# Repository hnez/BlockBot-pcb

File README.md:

BlockBot - Housing 3D-Designs
=============================

This repository contains all PCB design files.

All designs are created with the KiCad EDA suite.

The directory structure is as follow:

- blocks - Brick PCB
- dk_base - Millable PCB for the "denmark base" robot
- panel - Panelized layout that combines bricks and remote into a single file for cheaper ordering
- remote - Collector unit PCB

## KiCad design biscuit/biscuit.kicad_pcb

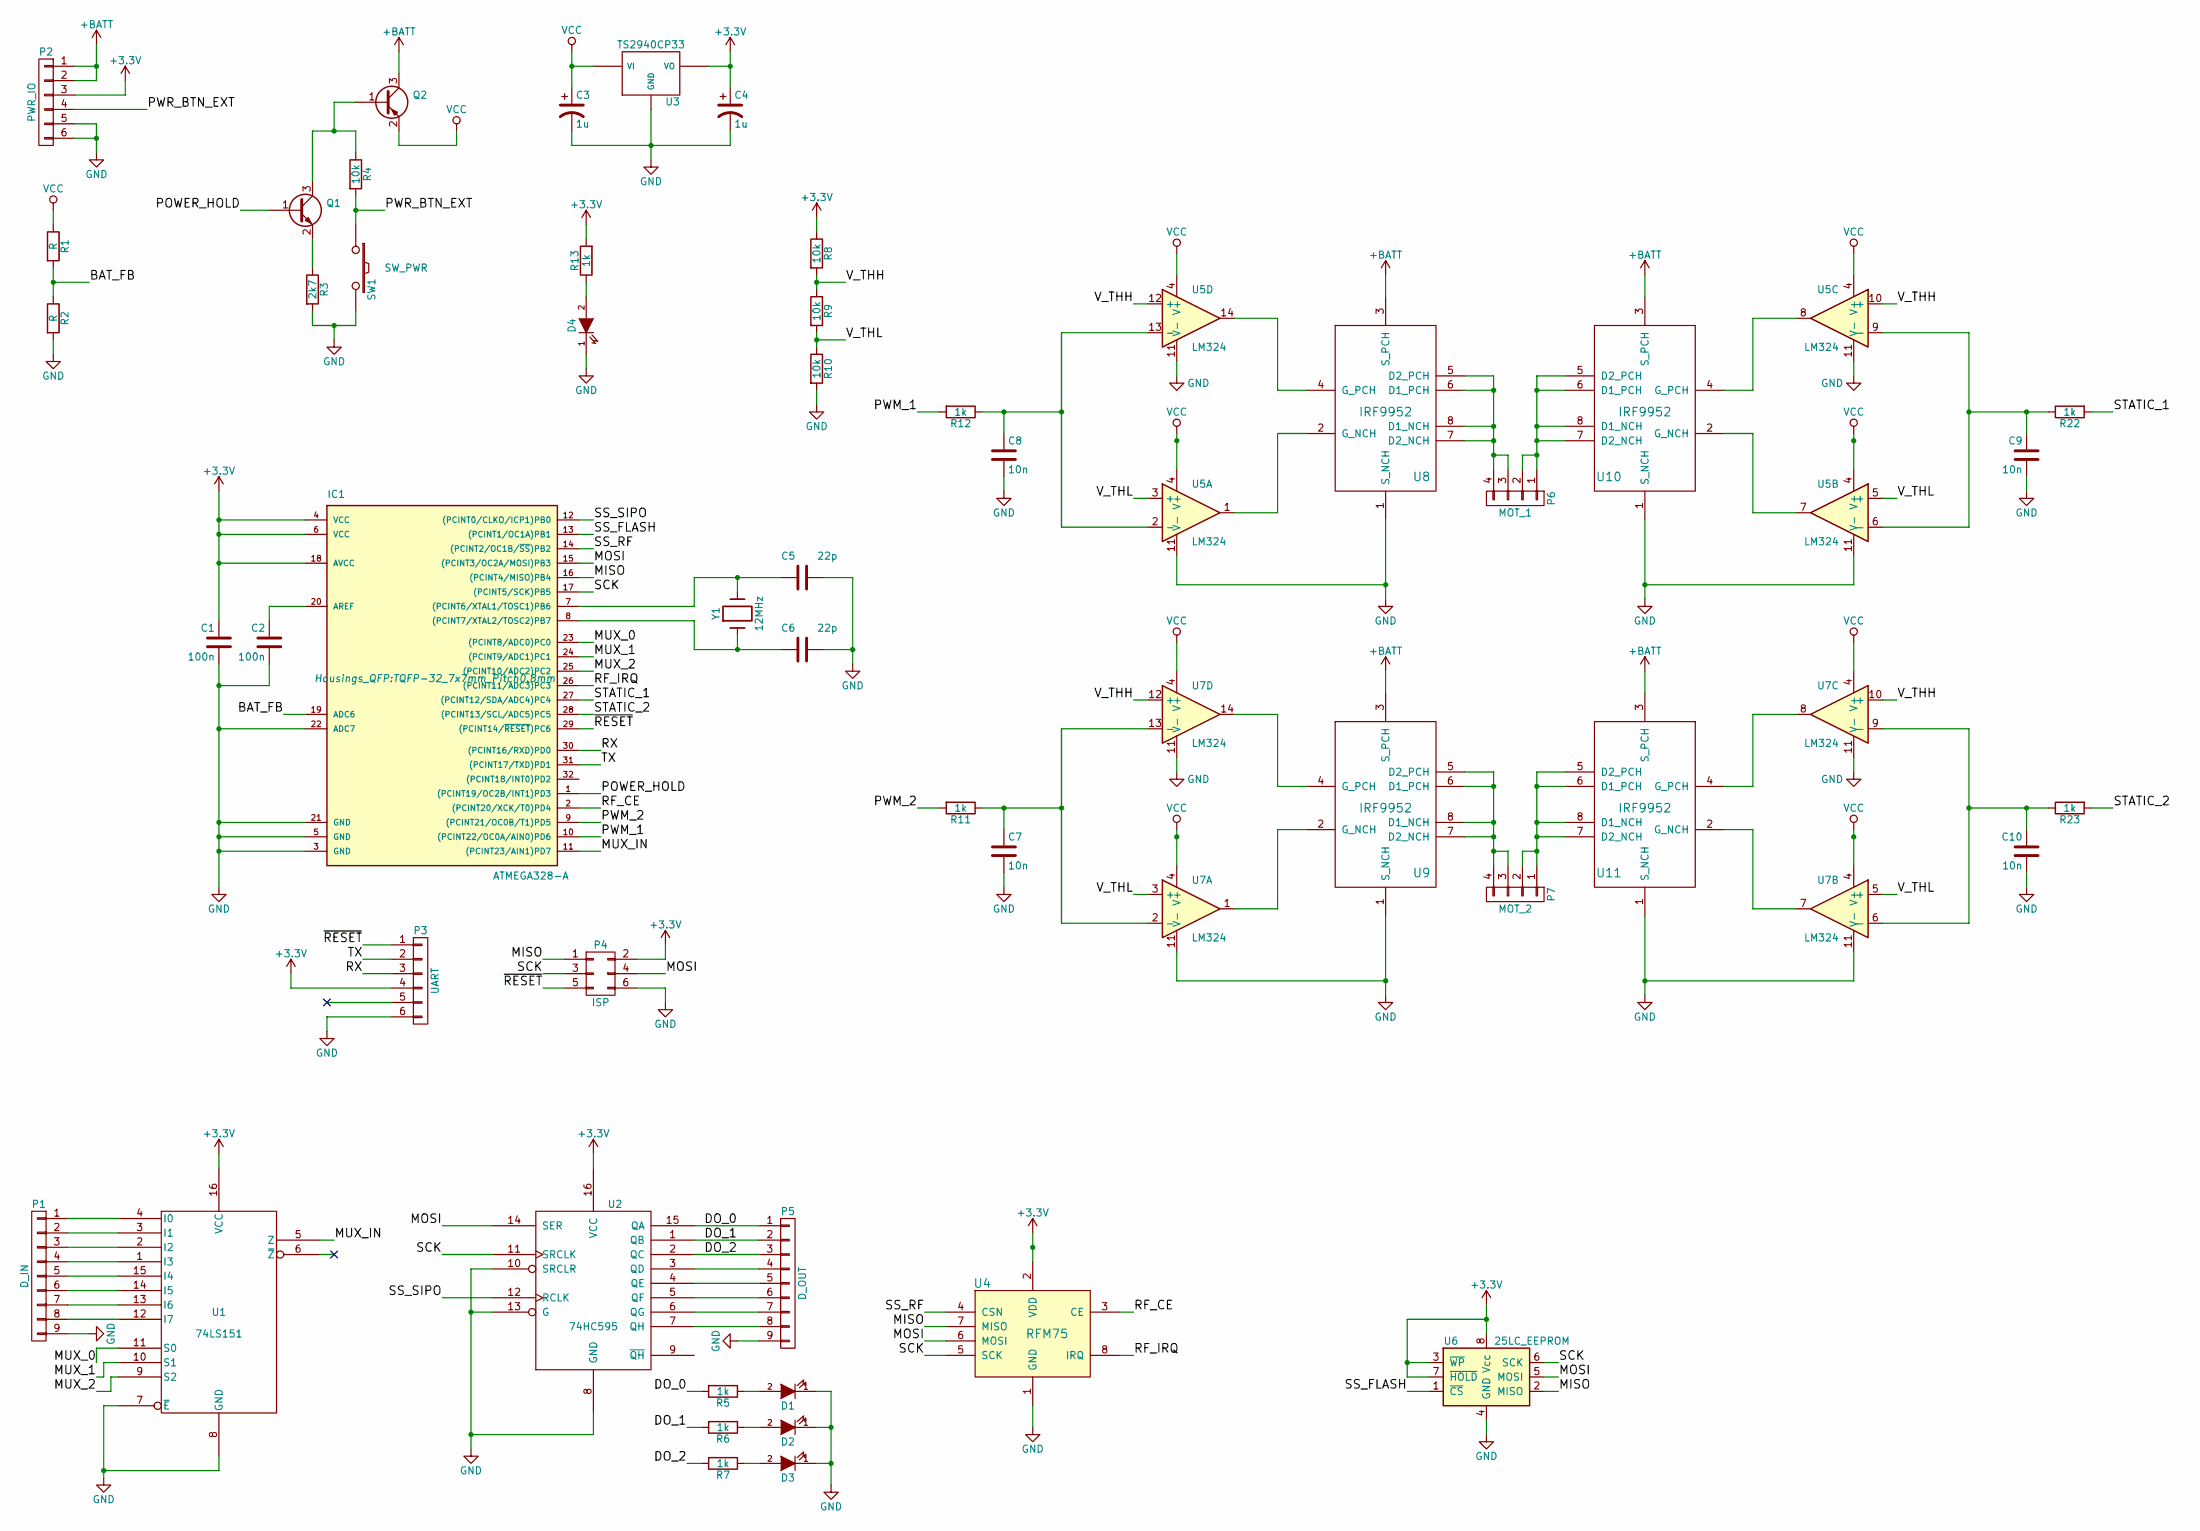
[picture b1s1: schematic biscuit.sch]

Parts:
C1, C2: 100n; C_0805
C3, C4: 1u; TantalC_SizeA_EIA-3216_Reflow
C5, C6: 22p; C_0805
C7, C8, C9, C10: 10n; C_0805
D1, D2, D3, D4: LED; LED_0805
IC1: ATMEGA328-A; TQFP-32_7x7mm_Pitch0.8mm
P1: D_IN; Pin_Header_Straight_1x09
P2: PWR_IO; Pin_Header_Straight_1x06
P3: UART; Pin_Header_Straight_1x06
P4: ISP; Pin_Header_Straight_2x03
P5: D_OUT; Pin_Header_Straight_1x09
P6: MOT_1; Pin_Header_Straight_1x04
P7: MOT_2; Pin_Header_Straight_1x04
Q1: Q_NPN_BEC; SOT-23
Q2: Q_PNP_BEC; SOT-23
R1, R2: R; R_0805
R3: 2k7; R_0805
R4, R8, R9, R10: 10k; R_0805
R5, R6, R7, R11, R12, R13, R22, R23: 1k; R_0805
SW1: SW_PWR; Schurter_LSG_1301
U1: 74LS151; SO-16-N
U2: 74HC595; SO-16-N
U3: TS2940CP33; TO-252-2Lead
U4: RFM75
U5, U7: LM324; SOIC-14_N
U6: 25LC_EEPROM; SOIC-8-N
U8, U9, U10, U11: IRF9952; SOIC-8-N
Y1: 12MHz; Crystal_HC49-SD_SMD

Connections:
+3V3: C1.1, C4.1, IC1.4 (VCC), IC1.6 (VCC), IC1.18 (AVCC), P2.3, P3.4, P4.2, R8.1, R13.2, U1.16 (VCC), U2.16 (VCC), U3.3 (VO), U4.2 (VDD), U6.3 (~WP), U6.7 (~HOLD), U6.8 (Vcc)
+BATT: P2.1, P2.2, Q2.3 (C), U8.3 (S_PCH), U9.3 (S_PCH), U10.3 (S_PCH), U11.3 (S_PCH)
/BAT_FB: IC1.19 (ADC6), R1.2, R2.1
/DO_0: P5.1, R5.2, U2.15 (QA)
/DO_1: P5.2, R6.2, U2.1 (QB)
/DO_2: P5.3, R7.2, U2.2 (QC)
/MISO: IC1.16 ((PCINT4/MISO)PB4), P4.1, U4.7 (MISO), U6.2 (MISO)
/MOSI: IC1.15 ((PCINT3/OC2A/MOSI)PB3), P4.4, U2.14 (SER), U4.6 (MOSI), U6.5 (MOSI)
/MUX_0: IC1.23 ((PCINT8/ADC0)PC0), U1.11 (S0)
/MUX_1: IC1.24 ((PCINT9/ADC1)PC1), U1.10 (S1)
/MUX_2: IC1.25 ((PCINT10/ADC2)PC2), U1.9 (S2)
/MUX_IN: IC1.11 ((PCINT23/AIN1)PD7), U1.5 (Z)
/POWER_HOLD: IC1.1 ((PCINT19/OC2B/INT1)PD3), Q1.1 (B)
/PWM_1: IC1.10 ((PCINT22/OC0A/AIN0)PD6), R12.2
/PWM_2: IC1.9 ((PCINT21/OC0B/T1)PD5), R11.2
/PWR_BTN_EXT: P2.4, R4.2, SW1.1
/RF_CE: IC1.2 ((PCINT20/XCK/T0)PD4), U4.3 (CE)
/RF_IRQ: IC1.26 ((PCINT11/ADC3)PC3), U4.8 (IRQ)
/RX: IC1.30 ((PCINT16/RXD)PD0), P3.3
/SCK: IC1.17 ((PCINT5/SCK)PB5), P4.3, U2.11 (SRCLK), U4.5 (SCK), U6.6 (SCK)
/SS_FLASH: IC1.13 ((PCINT1/OC1A)PB1), U6.1 (~CS)
/SS_RF: IC1.14 ((PCINT2/OC1B/~SS~)PB2), U4.4 (CSN)
/SS_SIPO: IC1.12 ((PCINT0/CLKO/ICP1)PB0), U2.12 (RCLK)
/STATIC_1: IC1.27 ((PCINT12/SDA/ADC4)PC4), R22.2
/STATIC_2: IC1.28 ((PCINT13/SCL/ADC5)PC5), R23.2
/TX: IC1.31 ((PCINT17/TXD)PD1), P3.2
/V_THH: R8.2, R9.1, U5.10 (+), U5.12 (+), U7.10 (+), U7.12 (+)
/V_THL: R9.2, R10.1, U5.3 (+), U5.5 (+), U7.3 (+), U7.5 (+)
/~RESET: IC1.29 ((PCINT14/~RESET~)PC6), P3.1, P4.5
GND: C1.2, C2.2, C3.2, C4.2, C5.1, C6.1, C7.2, C8.2, C9.2, C10.2, D1.1 (K), D2.1 (K), D3.1 (K), D4.1 (K), IC1.3 (GND), IC1.5 (GND), IC1.21 (GND), IC1.22 (ADC7), P1.9, P2.5, P2.6, P3.6, P4.6, P5.9, R2.2, R3.2, R10.2, SW1.2, U1.7 (~E), U1.8 (GND), U2.8 (GND), U2.10 (SRCLR), U2.13 (G), U3.2 (GND), U4.1 (GND), U5.11 (V-), U6.4 (GND), U7.11 (V-), U8.1 (S_NCH), U9.1 (S_NCH), U10.1 (S_NCH), U11.1 (S_NCH)
unnamed: C2.1, IC1.20 (AREF)
unnamed: C5.2, IC1.7 ((PCINT6/XTAL1/TOSC1)PB6), Y1.2
unnamed: C6.2, IC1.8 ((PCINT7/XTAL2/TOSC2)PB7), Y1.1
unnamed: C7.1, R11.1, U7.2 (-), U7.13 (-)
unnamed: C8.1, R12.1, U5.2 (-), U5.13 (-)
unnamed: C9.1, R22.1, U5.6 (-), U5.9 (-)
unnamed: C10.1, R23.1, U7.6 (-), U7.9 (-)
unnamed: D1.2 (A), R5.1
unnamed: D2.2 (A), R6.1
unnamed: D3.2 (A), R7.1
unnamed: D4.2 (A), R13.1
unnamed: P1.1, U1.4 (I0)
unnamed: P1.2, U1.3 (I1)
unnamed: P1.3, U1.2 (I2)
unnamed: P1.4, U1.1 (I3)
unnamed: P1.5, U1.15 (I4)
unnamed: P1.6, U1.14 (I5)
unnamed: P1.7, U1.13 (I6)
unnamed: P1.8, U1.12 (I7)
unnamed: P5.4, U2.3 (QD)
unnamed: P5.5, U2.4 (QE)
unnamed: P5.6, U2.5 (QF)
unnamed: P5.7, U2.6 (QG)
unnamed: P5.8, U2.7 (QH)
unnamed: P6.1, P6.2, U10.5 (D2_PCH), U10.6 (D1_PCH), U10.7 (D2_NCH), U10.8 (D1_NCH)
unnamed: P6.3, P6.4, U8.5 (D2_PCH), U8.6 (D1_PCH), U8.7 (D2_NCH), U8.8 (D1_NCH)
unnamed: P7.1, P7.2, U11.5 (D2_PCH), U11.6 (D1_PCH), U11.7 (D2_NCH), U11.8 (D1_NCH)
unnamed: P7.3, P7.4, U9.5 (D2_PCH), U9.6 (D1_PCH), U9.7 (D2_NCH), U9.8 (D1_NCH)
unnamed: Q1.2 (E), R3.1
unnamed: Q1.3 (C), Q2.1 (B), R4.1
unnamed: U5.1, U8.2 (G_NCH)
unnamed: U5.14, U8.4 (G_PCH)
unnamed: U7.1, U9.2 (G_NCH)
unnamed: U7.14, U9.4 (G_PCH)
unnamed: U5.7, U10.2 (G_NCH)
unnamed: U5.8, U10.4 (G_PCH)
unnamed: U7.7, U11.2 (G_NCH)
unnamed: U7.8, U11.4 (G_PCH)
VCC: C3.1, Q2.2 (E), R1.1, U3.1 (VI), U5.4 (V+), U7.4 (V+)

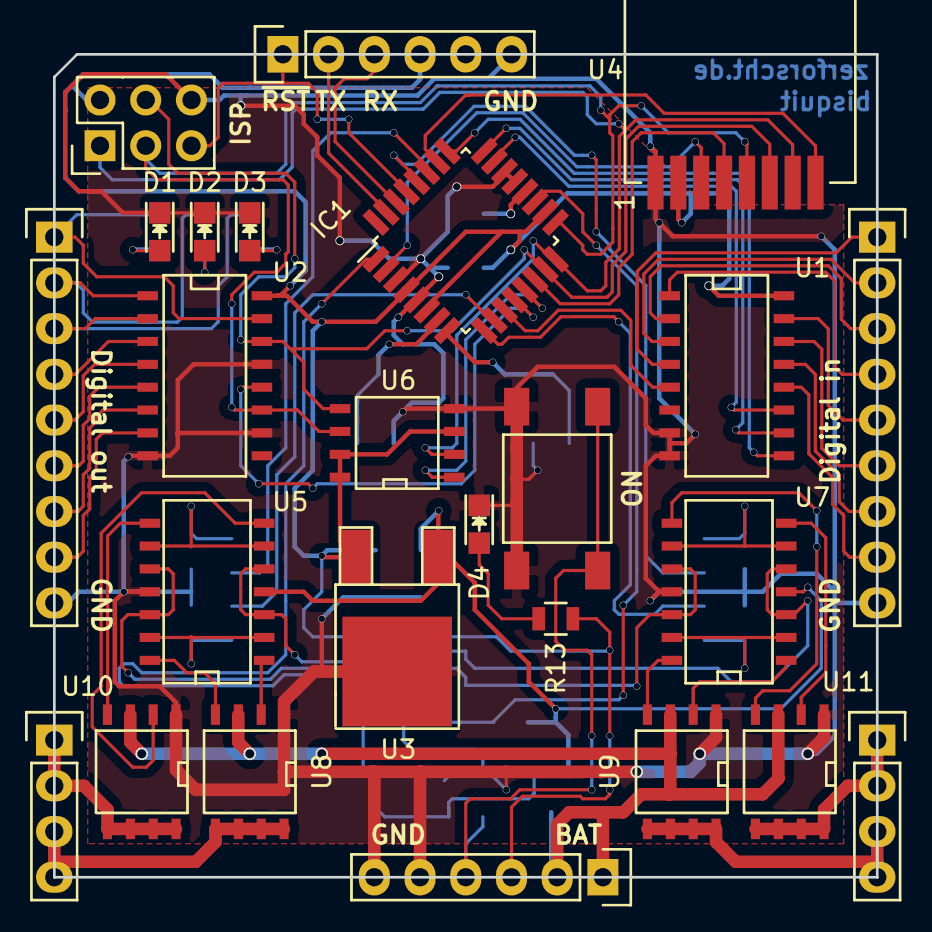
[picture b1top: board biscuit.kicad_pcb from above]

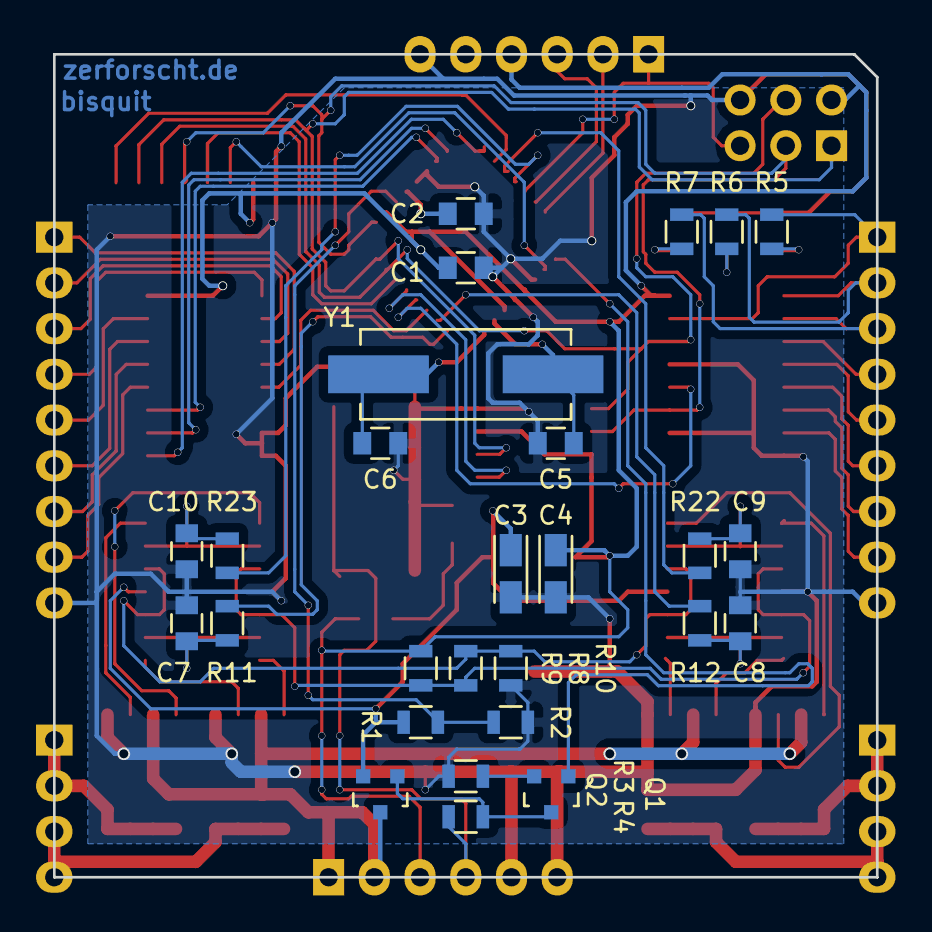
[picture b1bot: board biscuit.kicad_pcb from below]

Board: 2 copper layers, 45.7 x 45.7 mm, 52 parts (27 on the bottom side), 69 nets.

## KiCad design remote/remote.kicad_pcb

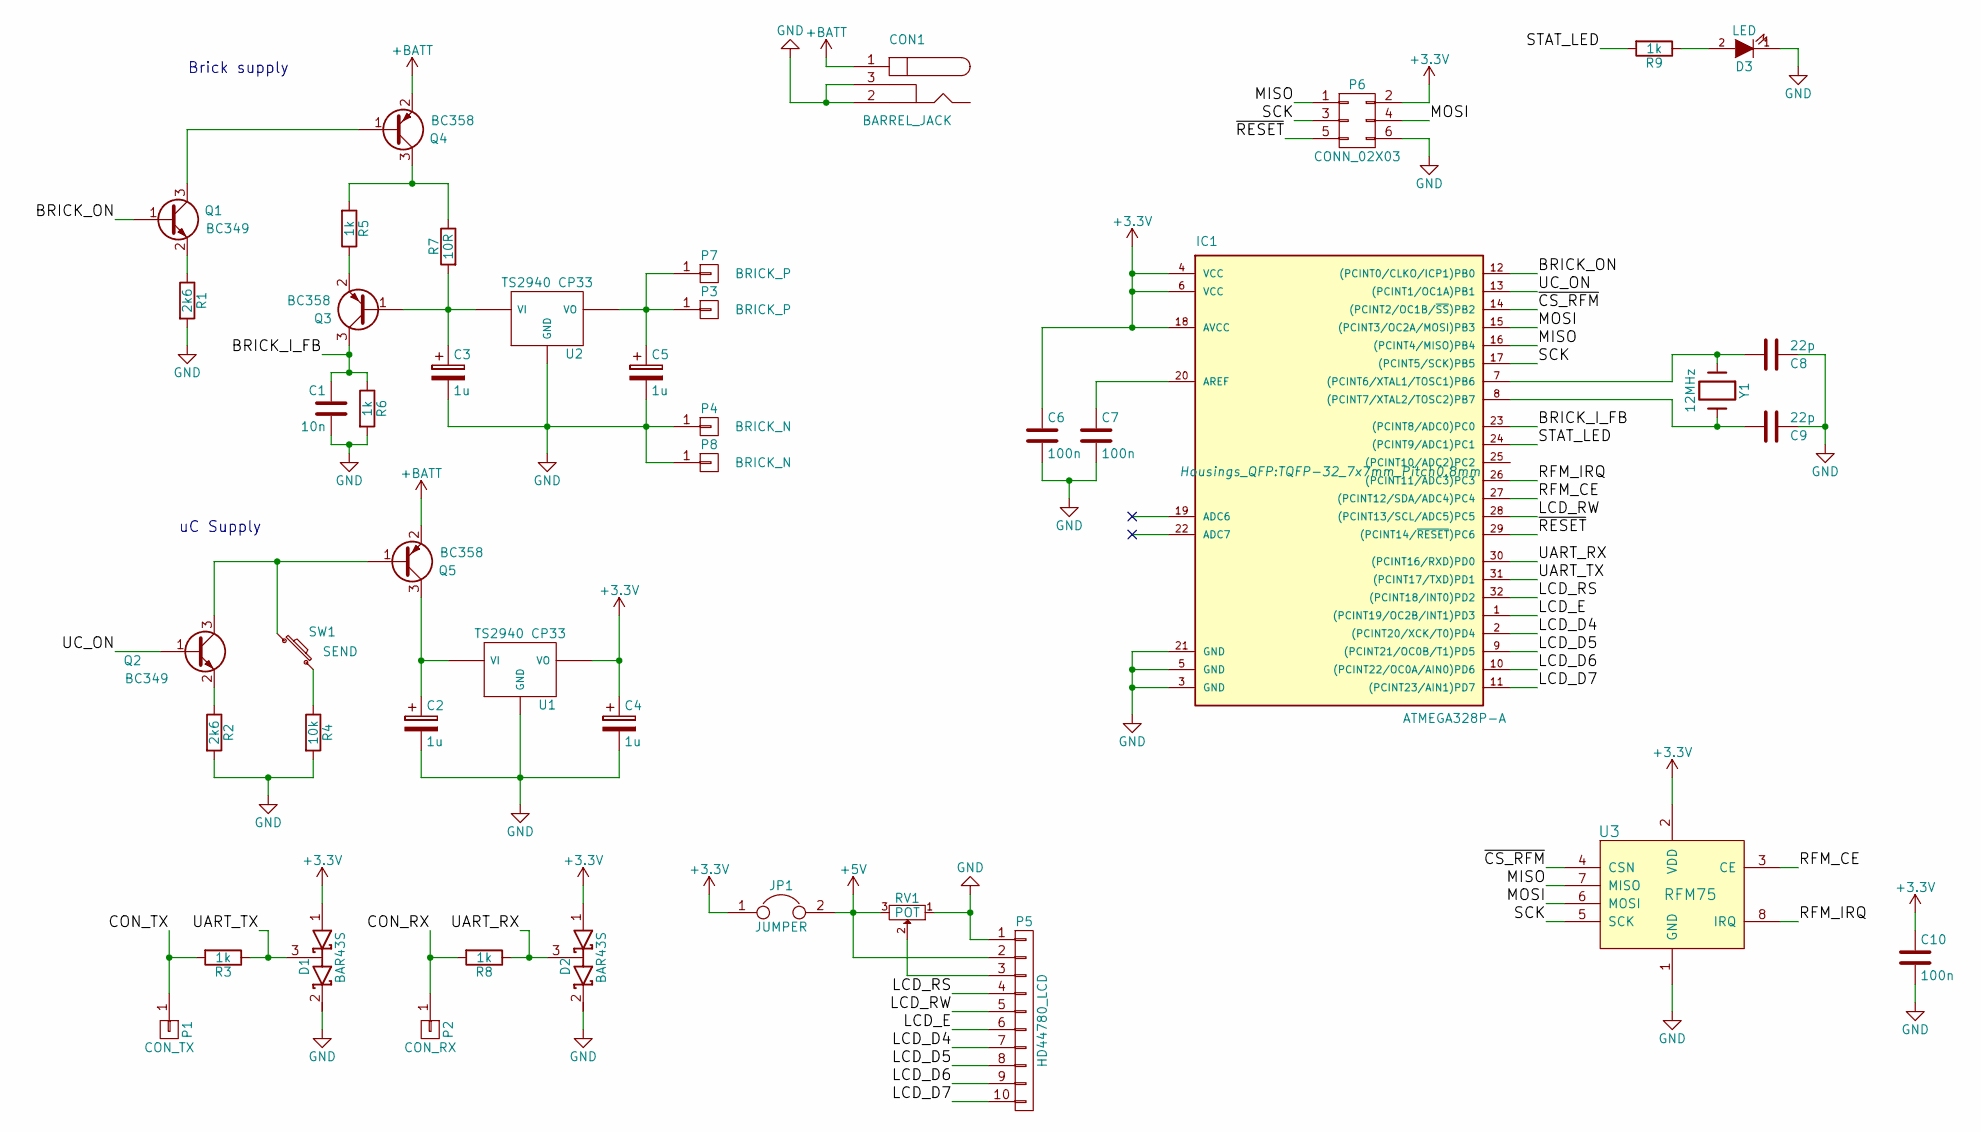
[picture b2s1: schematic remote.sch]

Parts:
C1: 10n; C_0805_HandSoldering
C2, C3, C4, C5: 1u; TantalC_SizeA_EIA-3216_HandSoldering
C6, C7, C10: 100n; C_0805_HandSoldering
C8, C9: 22p; C_0805_HandSoldering
CON1: BARREL_JACK
D1, D2: BAR43S; SOT-23
D3: LED; LED-3MM
IC1: ATMEGA328P-A; TQFP-32_7x7mm_Pitch0.8mm
JP1: JUMPER; R_0805_HandSoldering
P1: CON_TX; SmallFoilCon
P2: CON_RX; SmallFoilCon
P3, P7: BRICK_P; SmallFoilCon
P4, P8: BRICK_N; BigFoilCon
P5: HD44780_LCD; Pin_Header_Straight_1x10
P6: CONN_02X03; Pin_Header_Straight_2x03
Q1, Q2: BC349; SOT-23
Q3, Q4, Q5: BC358; SOT-23
R1, R2: 2k6; R_0805_HandSoldering
R3, R5, R6, R8, R9: 1k; R_0805_HandSoldering
R4: 10k; R_0805_HandSoldering
R7: 10R; R_0805_HandSoldering
RV1: POT; Cermet_Model23
SW1: SEND; Schurter_LSG_1301
U1, U2: TS2940 CP33; TO-252-2Lead
U3: RFM75
Y1: 12MHz; Crystal_HC49-U_Vertical

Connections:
+3V3: C4.1, C6.1, C10.1, D1.1 (A), D2.1 (A), IC1.4 (VCC), IC1.6 (VCC), IC1.18 (AVCC), JP1.1, P6.2, U1.VO, U3.2 (VDD)
+5V: JP1.2, P5.2, RV1.3
+BATT: CON1.1, Q4.2 (E), Q5.2 (E)
/BRICK_I_FB: C1.1, IC1.23 ((PCINT8/ADC0)PC0), Q3.3 (C), R6.1
/BRICK_ON: IC1.12 ((PCINT0/CLKO/ICP1)PB0), Q1.1 (B)
/CON_RX: P2.1, R8.2
/CON_TX: P1.1, R3.2
/LCD_D4: IC1.2 ((PCINT20/XCK/T0)PD4), P5.7
/LCD_D5: IC1.9 ((PCINT21/OC0B/T1)PD5), P5.8
/LCD_D6: IC1.10 ((PCINT22/OC0A/AIN0)PD6), P5.9
/LCD_D7: IC1.11 ((PCINT23/AIN1)PD7), P5.10
/LCD_E: IC1.1 ((PCINT19/OC2B/INT1)PD3), P5.6
/LCD_RS: IC1.32 ((PCINT18/INT0)PD2), P5.4
/LCD_RW: IC1.28 ((PCINT13/SCL/ADC5)PC5), P5.5
/MISO: IC1.16 ((PCINT4/MISO)PB4), P6.1, U3.7 (MISO)
/MOSI: IC1.15 ((PCINT3/OC2A/MOSI)PB3), P6.4, U3.6 (MOSI)
/RFM_CE: IC1.27 ((PCINT12/SDA/ADC4)PC4), U3.3 (CE)
/RFM_IRQ: IC1.26 ((PCINT11/ADC3)PC3), U3.8 (IRQ)
/SCK: IC1.17 ((PCINT5/SCK)PB5), P6.3, U3.5 (SCK)
/STAT_LED: IC1.24 ((PCINT9/ADC1)PC1), R9.2
/UART_RX: D2.3 (common), IC1.30 ((PCINT16/RXD)PD0), R8.1
/UART_TX: D1.3 (common), IC1.31 ((PCINT17/TXD)PD1), R3.1
/UC_ON: IC1.13 ((PCINT1/OC1A)PB1), Q2.1 (B)
/~CS_RFM: IC1.14 ((PCINT2/OC1B/~SS~)PB2), U3.4 (CSN)
/~RESET: IC1.29 ((PCINT14/~RESET~)PC6), P6.5
GND: C1.2, C2.2, C3.2, C4.2, C5.2, C6.2, C7.2, C8.1, C9.1, C10.2, CON1.2, CON1.3, D1.2 (K), D2.2 (K), D3.1 (K), IC1.3 (GND), IC1.5 (GND), IC1.21 (GND), P4.1, P5.1, P6.6, P8.1, R1.2, R2.2, R4.2, R6.2, RV1.1, U1.GND, U2.GND, U3.1 (GND)
unnamed: C2.1, Q5.3 (C), U1.VI
unnamed: C3.1, Q3.1 (B), R7.2, U2.VI
unnamed: C5.1, P3.1, P7.1, U2.VO
unnamed: C7.1, IC1.20 (AREF)
unnamed: C8.2, IC1.7 ((PCINT6/XTAL1/TOSC1)PB6), Y1.1
unnamed: C9.2, IC1.8 ((PCINT7/XTAL2/TOSC2)PB7), Y1.2
unnamed: D3.2 (A), R9.1
unnamed: P5.3, RV1.2
unnamed: Q1.2 (E), R1.1
unnamed: Q1.3 (C), Q4.1 (B)
unnamed: Q2.2 (E), R2.1
unnamed: Q2.3 (C), Q5.1 (B), SW1.1
unnamed: Q3.2 (E), R5.1
unnamed: Q4.3 (C), R5.2, R7.1
unnamed: R4.1, SW1.2

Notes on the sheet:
Brick supply
uC Supply

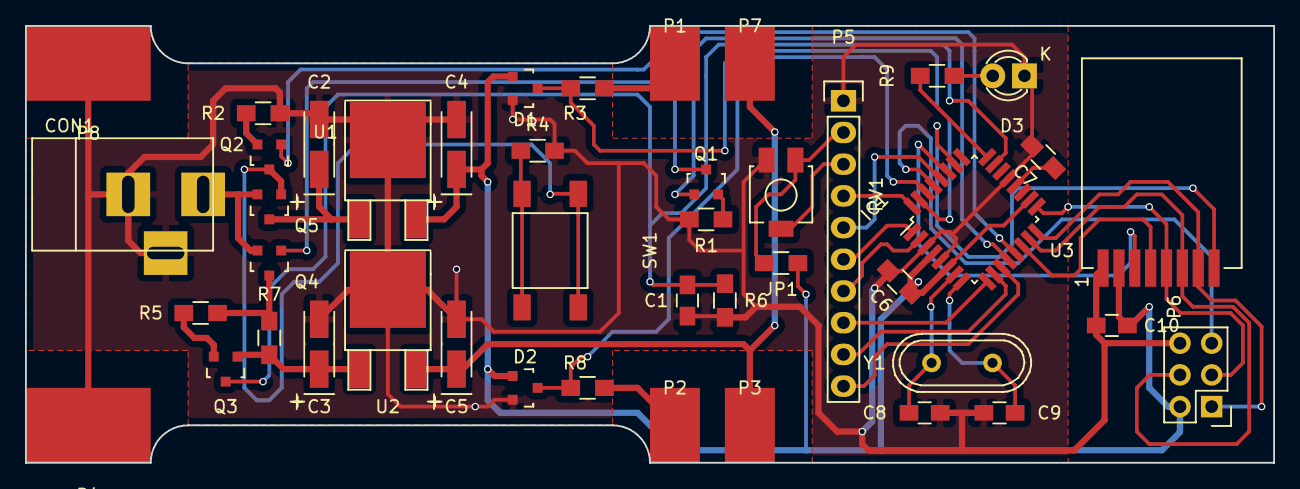
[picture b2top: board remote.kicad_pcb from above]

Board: 2 copper layers, 100.0 x 35.0 mm, 44 parts (0 on the bottom side), 41 nets.

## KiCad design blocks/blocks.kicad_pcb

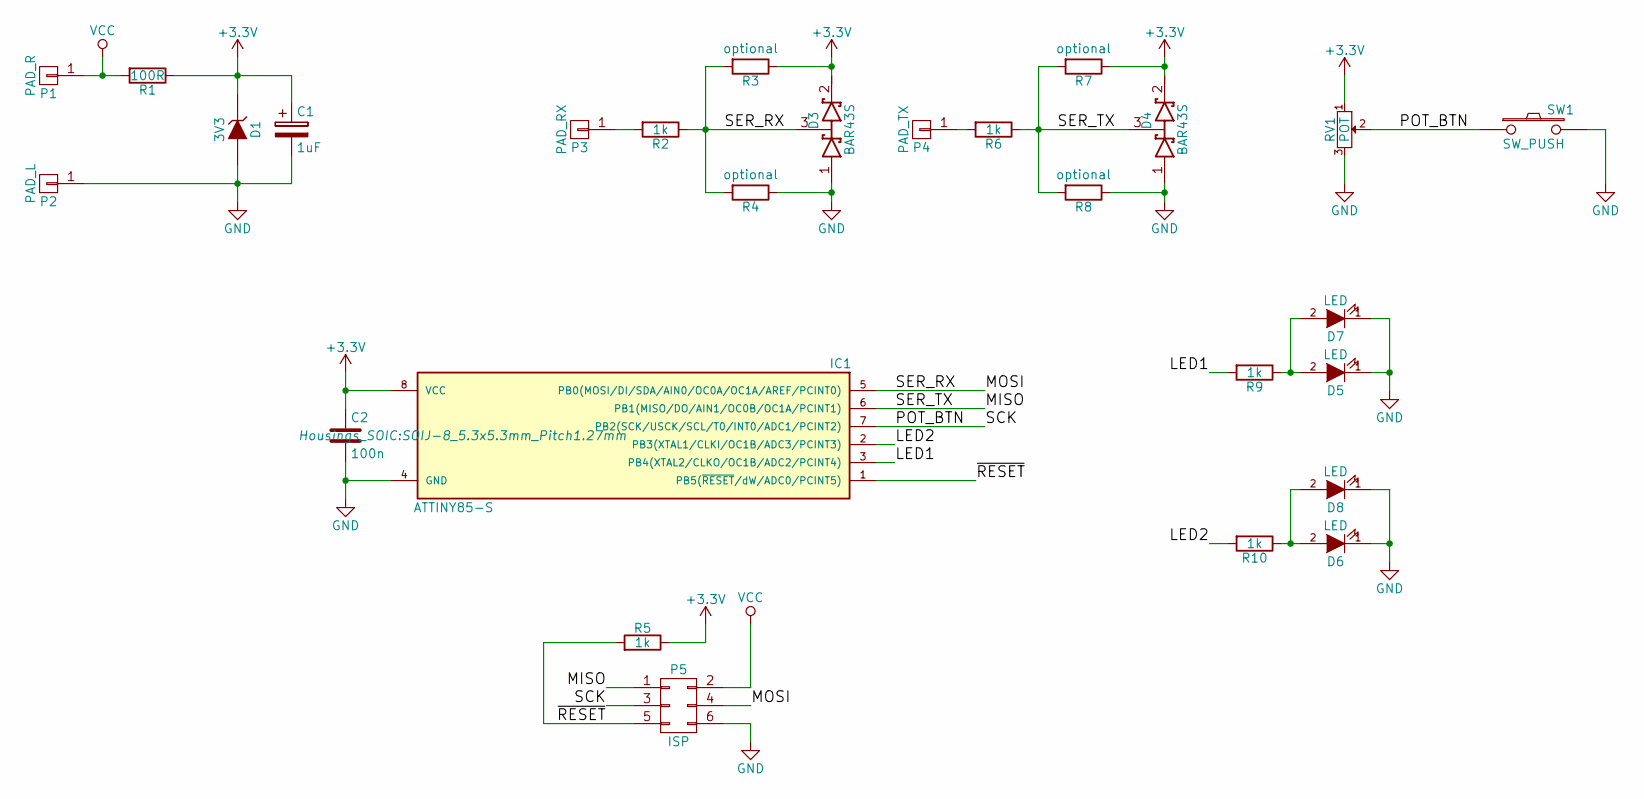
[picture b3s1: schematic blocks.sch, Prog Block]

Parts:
C1: 1uF; TantalC_SizeA_EIA-3216_HandSoldering
C2: 100n; C_0805_HandSoldering
D1: 3V3; SOT-23
D3, D4: BAR43S; SOT-23_Handsoldering
D5, D6: LED; LED-3MM
D7, D8: LED; LED_0805
IC1: ATTINY85-S; SOIJ-8_5.3x5.3mm_Pitch1.27mm
P1: PAD_R; BigPad
P2: PAD_L; HugePad
P3: PAD_RX; Smallpad
P4: PAD_TX; Smallpad
P5: ISP; Pin_Header_Straight_2x03
R1: 100R; R_0805_HandSoldering
R2, R5, R6, R9, R10: 1k; R_0805_HandSoldering
R3, R4, R7, R8: optional; R_0805_HandSoldering
RV1: POT; Cermet_Model23
SW1: SW_PUSH; Schurter_LSG_1301

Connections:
+3V3: C1.1, C2.1, D1.3 (K), D3.2 (K), D4.2 (K), IC1.8 (VCC), R1.1, R3.1, R5.1, R7.1, RV1.1
/LED1: IC1.3 (PB4(XTAL2/CLKO/OC1B/ADC2/PCINT4)), R9.2
/LED2: IC1.2 (PB3(XTAL1/CLKI/OC1B/ADC3/PCINT3)), R10.2
/MISO: D4.3 (common), IC1.6 (PB1(MISO/DO/AIN1/OC0B/OC1A/PCINT1)), P5.1, R6.1, R7.2, R8.2
/MOSI: D3.3 (common), IC1.5 (PB0(MOSI/DI/SDA/AIN0/OC0A/OC1A/AREF/PCI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), P5.4, R2.1, R3.2, R4.2
/POT_BTN: IC1.7 (PB2(SCK/USCK/SCL/T0/INT0/ADC1/PCINT2)), P5.3, RV1.2, SW1.1
/~RESET: IC1.1 (PB5(~RESET~/dW/ADC0/PCINT5)), P5.5, R5.2
GND: C1.2, C2.2, D1.1 (A), D3.1 (A), D4.1 (A), D5.1 (K), D6.1 (K), D7.1 (K), D8.1 (K), IC1.4 (GND), P2.1, P5.6, R4.1, R8.1, RV1.3, SW1.2
unnamed: D5.2 (A), D7.2 (A), R9.1
unnamed: D6.2 (A), D8.2 (A), R10.1
unnamed: P3.1, R2.2
unnamed: P4.1, R6.2
VCC: P1.1, P5.2, R1.2

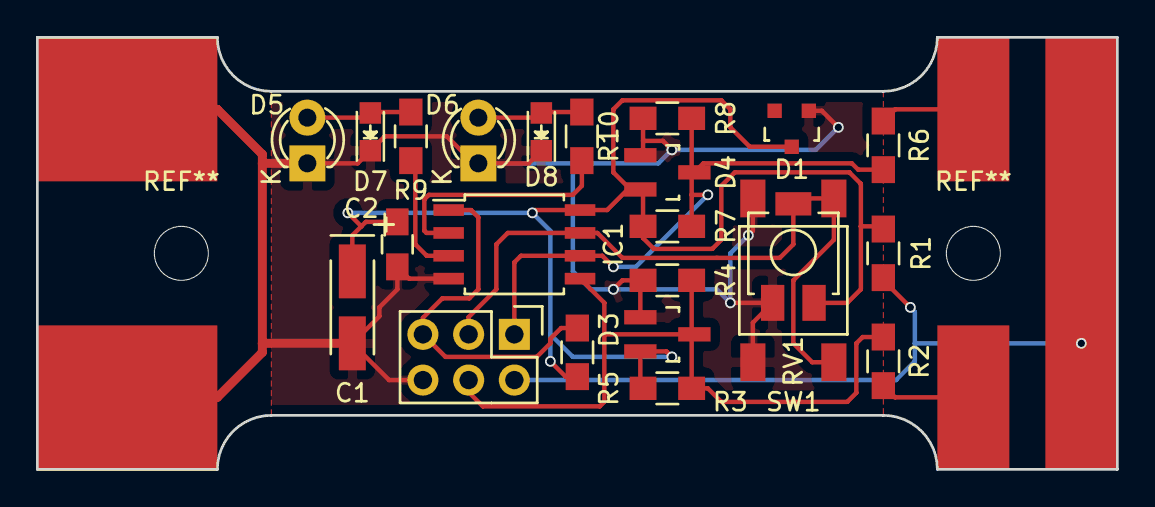
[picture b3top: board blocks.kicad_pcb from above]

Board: 2 copper layers, 60.0 x 24.0 mm, 27 parts (0 on the bottom side), 13 nets.

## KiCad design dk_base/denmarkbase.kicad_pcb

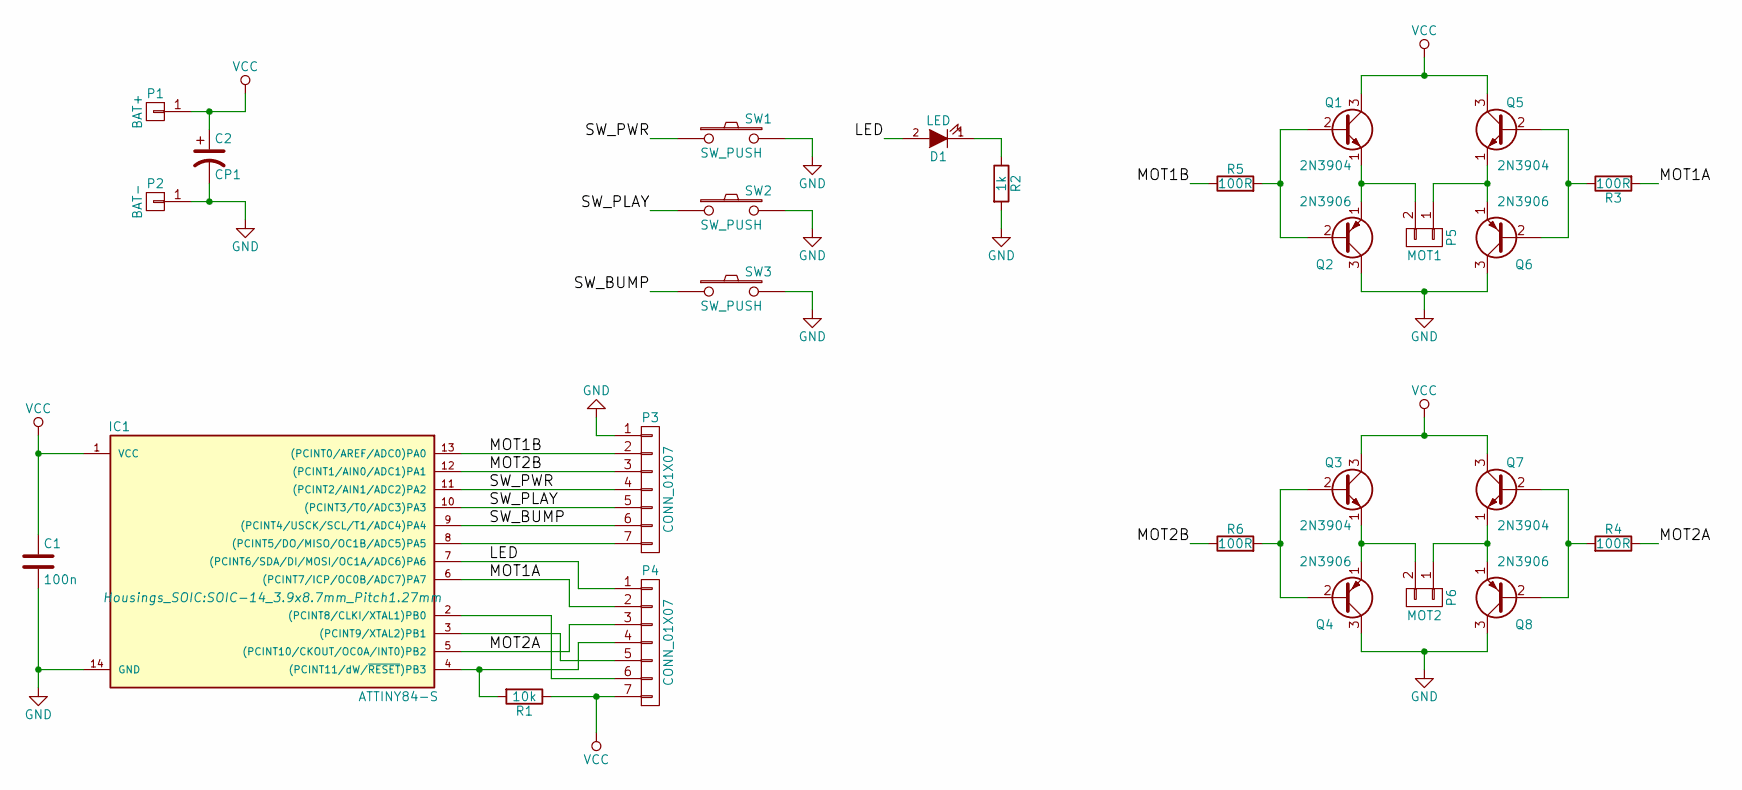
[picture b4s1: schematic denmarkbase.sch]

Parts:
C1: 100n; C_0805_HandSoldering
C2: CP1; C_Radial_D10_L16_P5
D1: LED; LED-3MM
IC1: ATTINY84-S; SOIC-14_3.9x8.7mm_Pitch1.27mm
P1: BAT+; BAT_CON
P2: BAT-; BAT_CON
P3, P4: CONN_01X07; Pin_Header_Straight_1x07
P5: MOT1; MOT
P6: MOT2; MOT
Q1, Q3, Q5, Q7: 2N3904; TO-92_Inline_Wide
Q2, Q4, Q6, Q8: 2N3906; TO-92_Inline_Wide
R1: 10k; Resistor_Horizontal_RM7mm
R2: 1k; Resistor_Horizontal_RM7mm
R3, R4, R5, R6: 100R; Resistor_Horizontal_RM7mm
SW1, SW2: SW_PUSH; BTN
SW3: SW_PUSH

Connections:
/LED: D1.2 (A), IC1.7 ((PCINT6/SDA/DI/MOSI/OC1A/ADC6)PA6), P4.1
/MOT1A: IC1.6 ((PCINT7/ICP/OC0B/ADC7)PA7), P4.2, R3.2
/MOT1B: IC1.13 ((PCINT0/AREF/ADC0)PA0), P3.2, R5.1
/MOT2A: IC1.5 ((PCINT10/CKOUT/OC0A/INT0)PB2), P4.3, R4.1
/MOT2B: IC1.12 ((PCINT1/AIN0/ADC1)PA1), P3.3, R6.1
/SW_BUMP: IC1.9 ((PCINT4/USCK/SCL/T1/ADC4)PA4), P3.6, SW3.1
/SW_PLAY: IC1.10 ((PCINT3/T0/ADC3)PA3), P3.5, SW2.1
/SW_PWR: IC1.11 ((PCINT2/AIN1/ADC2)PA2), P3.4, SW1.1
GND: C1.2, C2.2, IC1.14 (GND), P2.1, P3.1, Q2.3 (C), Q4.3 (C), Q6.3 (C), Q8.3 (C), R2.2, SW1.2, SW2.2, SW3.2
unnamed: D1.1 (K), R2.1
unnamed: IC1.2 ((PCINT8/CLKI/XTAL1)PB0), P4.6
unnamed: IC1.3 ((PCINT9/XTAL2)PB1), P4.5
unnamed: IC1.4 ((PCINT11/dW/~RESET~)PB3), P4.4, R1.2
unnamed: IC1.8 ((PCINT5/DO/MISO/OC1B/ADC5)PA5), P3.7
unnamed: P5.1, Q5.1 (E), Q6.1 (E)
unnamed: P5.2, Q1.1 (E), Q2.1 (E)
unnamed: P6.1, Q7.1 (E), Q8.1 (E)
unnamed: P6.2, Q3.1 (E), Q4.1 (E)
unnamed: Q1.2 (B), Q2.2 (B), R5.2
unnamed: Q3.2 (B), Q4.2 (B), R6.2
unnamed: Q5.2 (B), Q6.2 (B), R3.1
unnamed: Q7.2 (B), Q8.2 (B), R4.2
VCC: C1.1, C2.1, IC1.1 (VCC), P1.1, P4.7, Q1.3 (C), Q3.3 (C), Q5.3 (C), Q7.3 (C), R1.1

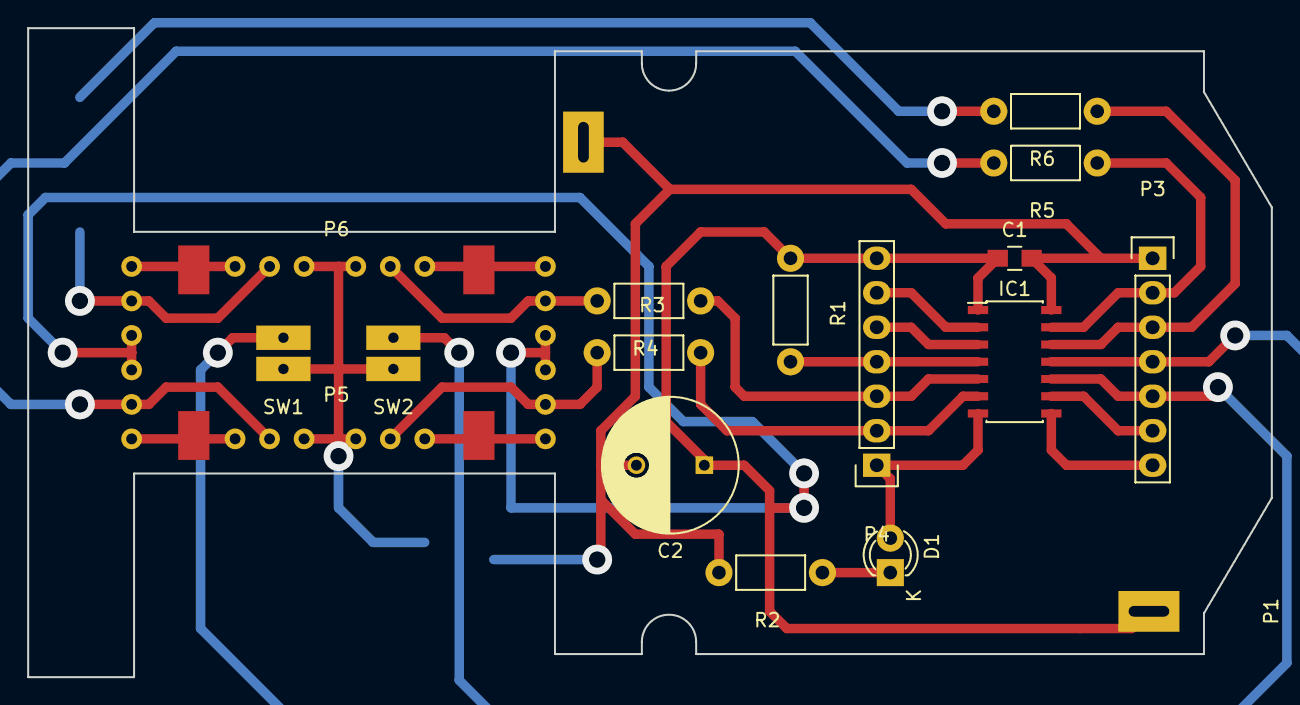
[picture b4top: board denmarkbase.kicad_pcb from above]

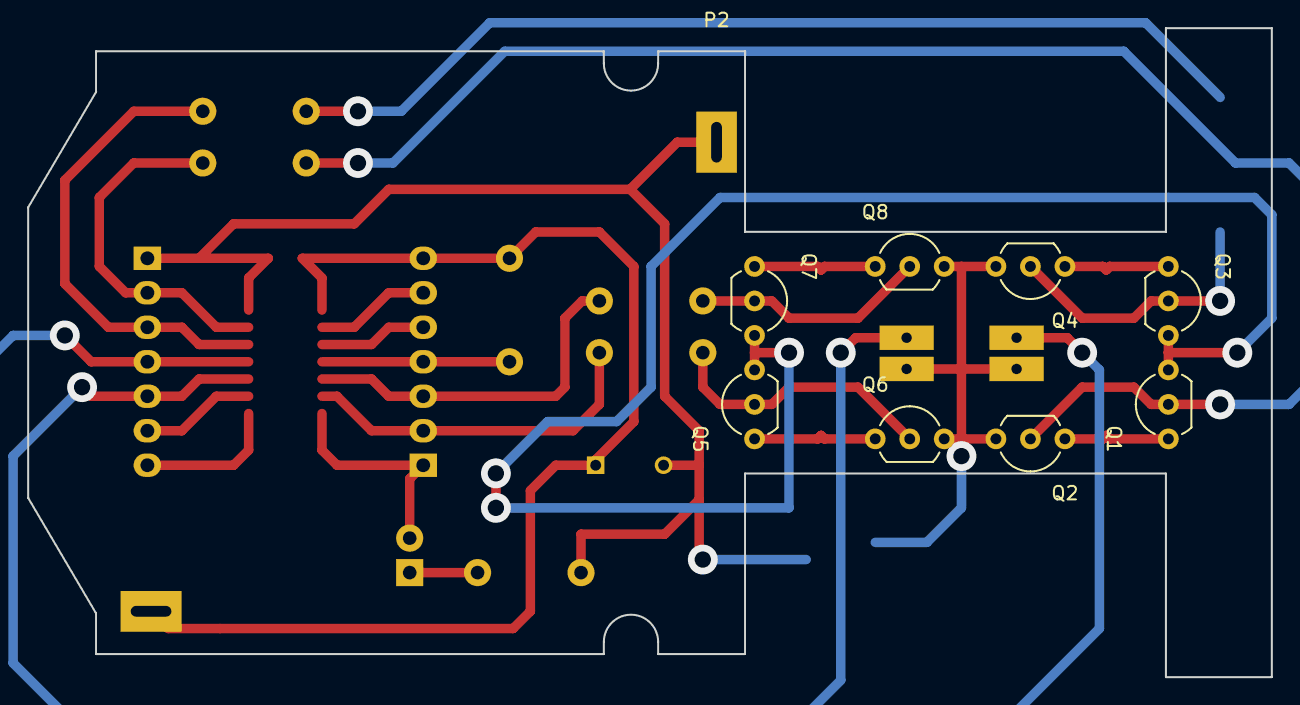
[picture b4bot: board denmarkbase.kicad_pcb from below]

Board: 2 copper layers, 91.6 x 47.8 mm, 26 parts (9 on the bottom side), 23 nets.

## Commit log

2016-04-24 Initial License commit
2016-04-24 Initial work on the block pcb
2016-04-24 Added name and domain to pcb
2016-04-25 Removed autogenerated netlist file
2016-04-25 Fixed wrong pull up reference for RESET input
2016-04-25 Started developing the remote control unit
    The Power supply for the blocks is overly complicated and batshit crazy.
2016-04-25 rationalized away one transistor
2016-04-28 Designed a Millable PCB to retrofit a Existing robot base.
2016-04-28 Excluded Generated Gerber files from git
2016-05-30 Added mounting holes and changed Zener diode on brick pcb
2016-05-30 Started over again with the remote controll
2016-05-31 Collecor unit WIP
2016-05-31 finished layouting the collector unit
2016-05-31 Panelized design for ordering
2016-06-30 Wrote a README file
2016-11-19 Started working on new robot meta platform "bisquit"
2016-11-28 PCB Routing for bisquit
2016-12-04 First sucessful route for bisquit board
2016-12-04 Routing cleanup
2016-12-04 Cleanup labels and add power LED
2016-12-04 Added labels
2016-12-04 Added reference to website
